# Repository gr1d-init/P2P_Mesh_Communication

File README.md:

# P2P_Mesh_Communication_Learning_Kit_SKEE1103_C_Programming_for_Engineers

For this project, our main targeted users were particularly the high school students who are able to comprehend most basic peer-to-peer mesh communication knowledge which often included in STEM subject syllabus such as Computer Science and Physics subject. 

Other than that, students are also exposed to an exciting involvement in Arduino kit development, lies under the usage of microcontrollers, which is a foundational skillset for their Reka Bentuk Teknologi subject that includes hardware and software implementations.

In short, we want student to head the ground up, build up a Peer-to-Peer Mesh Communication Device on their own with given instructions manual, enhance their practical skills on utilise a microcontroller and strengthen their understanding towards wireless communication protocols.

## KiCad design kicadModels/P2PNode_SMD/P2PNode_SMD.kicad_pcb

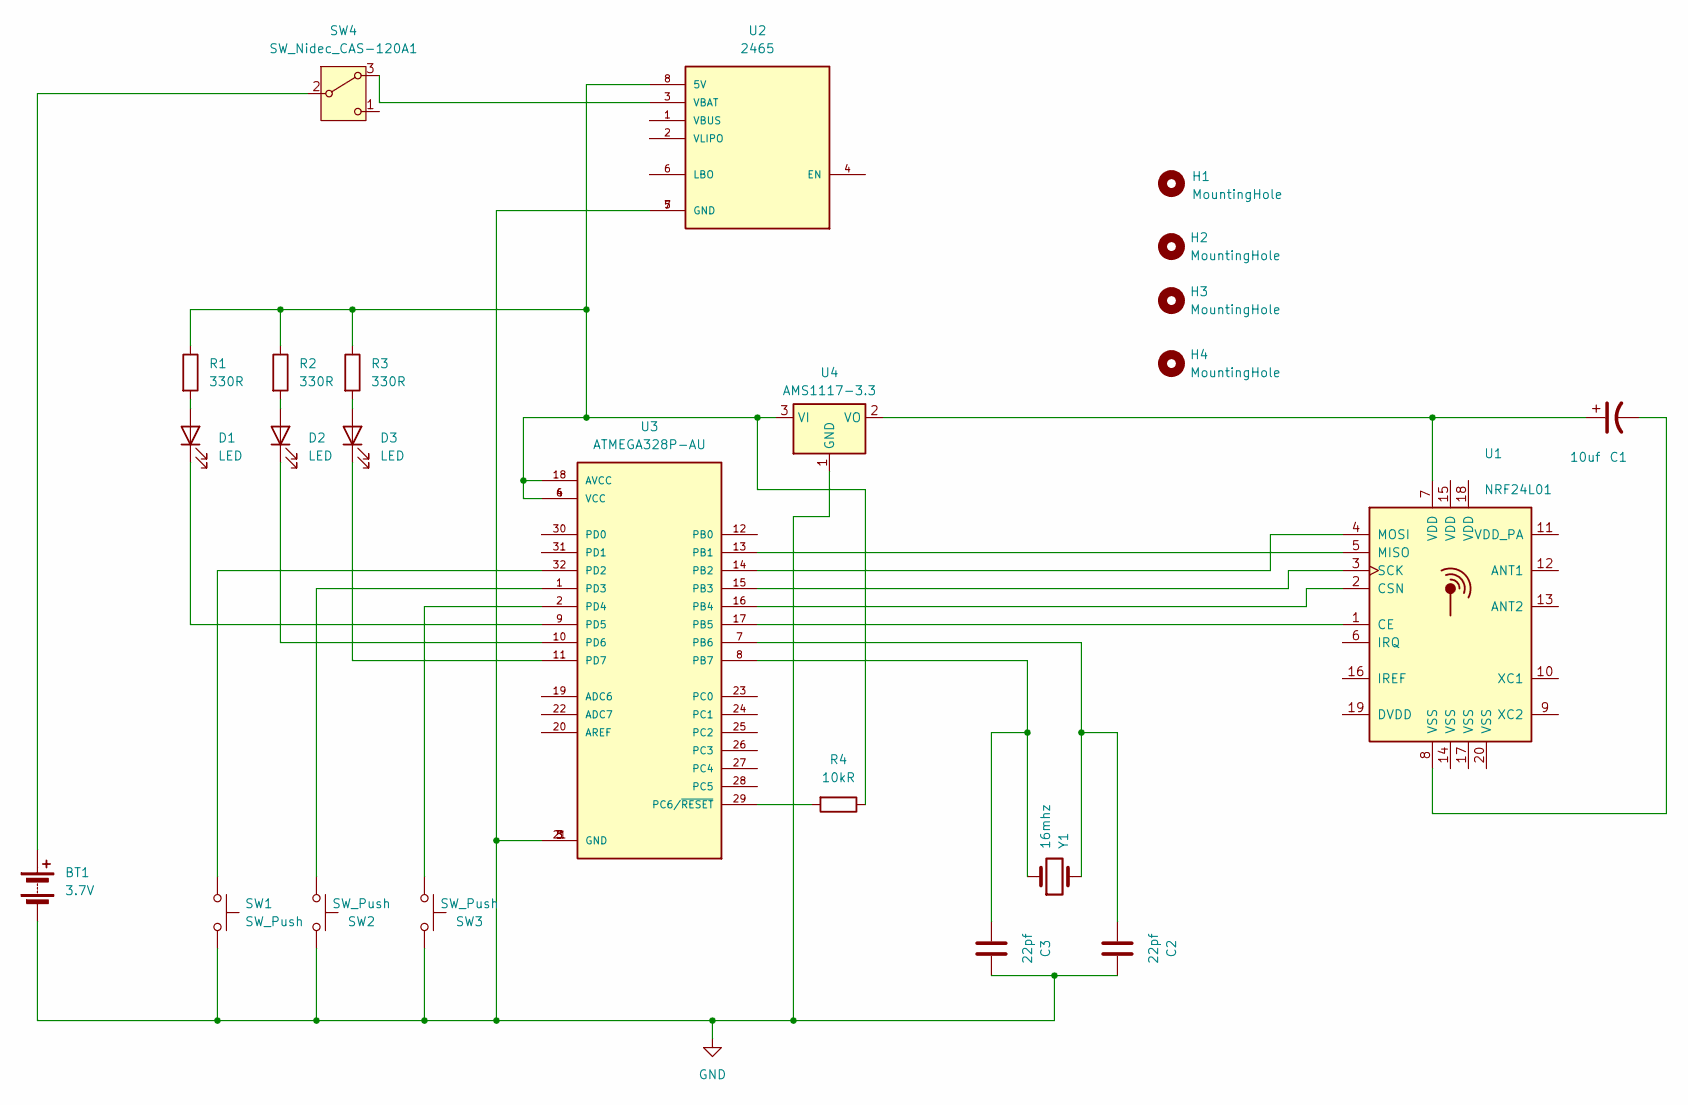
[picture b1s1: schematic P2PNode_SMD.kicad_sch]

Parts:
BT1: 3.7V; BatteryHolder_Keystone_1042_1x18650
C1: 10uf; C_0201_0603Metric
C2, C3: 22pf; C_0201_0603Metric
D1, D2, D3: LED; LED_1206_3216Metric
H1, H2, H3, H4: MountingHole; MountingHole_2.1mm
R1, R2, R3: 330R; R_0201_0603Metric
R4: 10kR; R_0201_0603Metric
SW1, SW2, SW3: SW_Push; SW_Push_1P1T_NO_CK_KMR2
SW4: SW_Nidec_CAS-120A1; Nidec_Copal_CAS-120A
U1: NRF24L01; QFN-20-1EP_4x4mm_P0.5mm_EP2.5x2.5mm
U2: 2465; MODULE_2465; PARTREV B
U3: ATMEGA328P-AU; QFP80P900X900X120-32N; PARTREV 8271A
U4: AMS1117-3.3; SOT-223-3_TabPin2
Y1: 16mhz; Crystal_SMD_Abracon_ABM7-2Pin_6.0x3.5mm

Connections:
GND: BT1.2 (-), C2.2, C3.2, SW1.2, SW2.2, SW3.2, U2.5 (GND), U2.7 (GND), U3.3 (GND), U3.5 (GND), U3.21 (GND), U4.1 (GND)
unnamed: BT1.1 (+), SW4.2 (B)
unnamed: C1.2, U1.8 (VSS)
unnamed: D1.2 (A), R1.2
unnamed: D1.1 (K), U3.9 (PD5)
unnamed: D2.2 (A), R2.2
unnamed: D2.1 (K), U3.10 (PD6)
unnamed: D3.2 (A), R3.2
unnamed: D3.1 (K), U3.11 (PD7)
unnamed: SW4.3 (A), U2.3 (VBAT)
unnamed: U1.1 (CE), U3.17 (PB5)
unnamed: U1.2 (CSN), U3.16 (PB4)
unnamed: U1.5 (MISO), U3.13 (PB1)
unnamed: U1.4 (MOSI), U3.14 (PB2)
unnamed: U1.3 (SCK), U3.15 (PB3)
unnamed: R1.1, R2.1, R3.1, R4.1, U2.8 (5V), U3.4 (VCC), U3.6 (VCC), U3.18 (AVCC), U4.3 (VI)
unnamed: C2.1, U3.7 (PB6), Y1.2
unnamed: C3.1, U3.8 (PB7), Y1.1
unnamed: R4.2, U3.29 (PC6/~RESET)
unnamed: SW1.1, U3.32 (PD2)
unnamed: SW2.1, U3.1 (PD3)
unnamed: SW3.1, U3.2 (PD4)
unnamed: C1.1, U1.7 (VDD), U4.2 (VO)

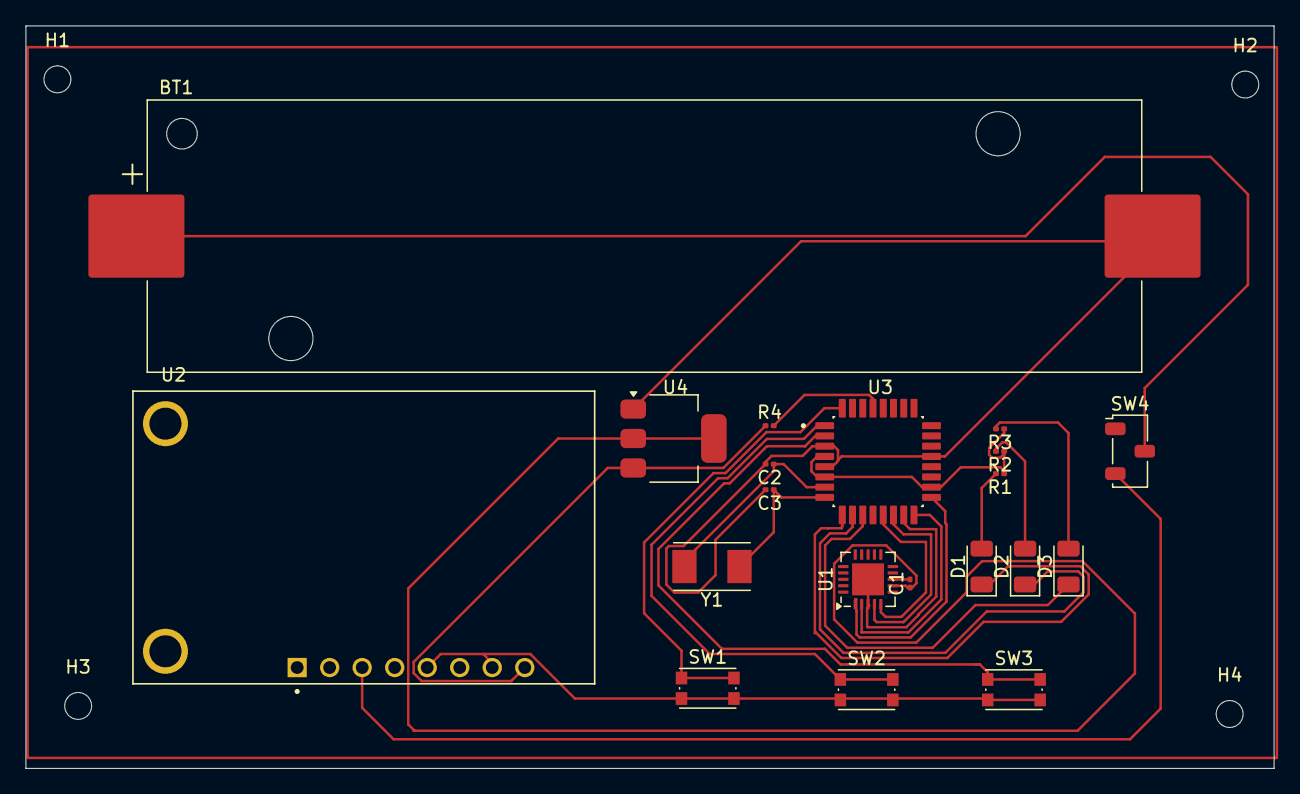
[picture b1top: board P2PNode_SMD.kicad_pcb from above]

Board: 2 copper layers, 97.5 x 58.0 mm, 24 parts (0 on the bottom side), 23 nets.

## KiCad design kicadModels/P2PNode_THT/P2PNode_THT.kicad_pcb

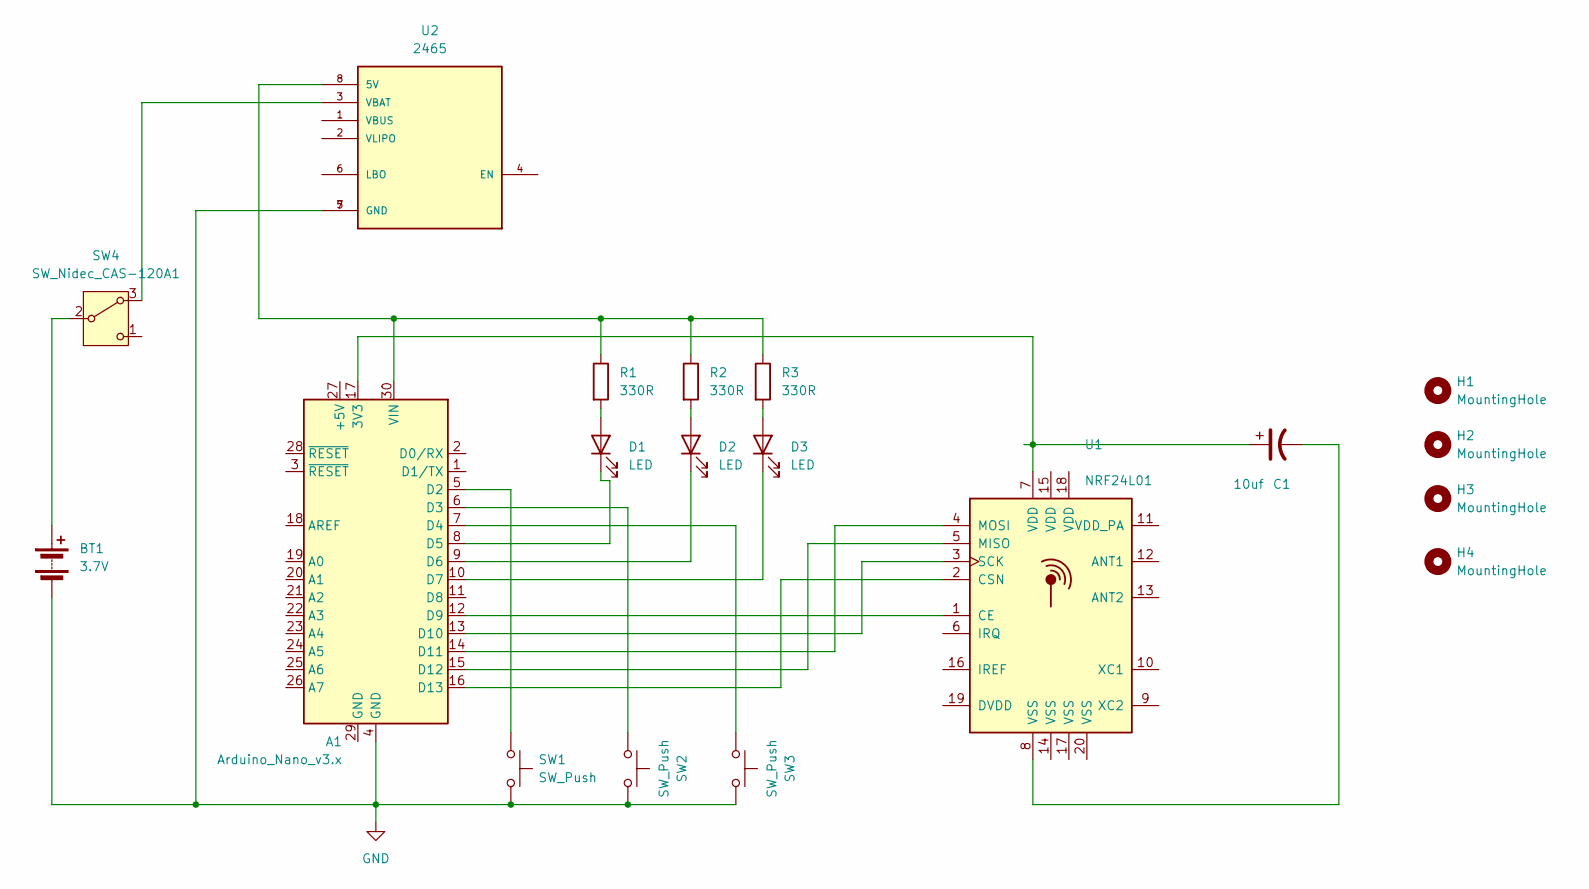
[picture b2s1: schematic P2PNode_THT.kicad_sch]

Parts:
A1: Arduino_Nano_v3.x; Arduino_Nano
BT1: 3.7V; BatteryHolder_Keystone_1042_1x18650
C1: 10uf; CP_Axial_L10.0mm_D4.5mm_P15.00mm_Horizontal
D1, D2, D3: LED; LED_D3.0mm
H1, H2, H3, H4: MountingHole; MountingHole_2.1mm
R1, R2, R3: 330R; R_Axial_DIN0204_L3.6mm_D1.6mm_P5.08mm_Horizontal
SW1, SW2, SW3: SW_Push; SW_PUSH_6mm_H5mm
SW4: SW_Nidec_CAS-120A1; Nidec_Copal_CAS-120A
U1: NRF24L01; QFN-20-1EP_4x4mm_P0.5mm_EP2.5x2.5mm
U2: 2465; MODULE_2465; PARTREV B

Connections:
GND: A1.4 (GND), BT1.2 (-), SW1.2, SW2.2, SW3.2, U2.5 (GND), U2.7 (GND)
unnamed: A1.17 (3V3), C1.1, U1.7 (VDD)
unnamed: A1.5 (D2), SW1.1
unnamed: A1.6 (D3), SW2.1
unnamed: A1.7 (D4), SW3.1
unnamed: A1.8 (D5), D1.1 (K)
unnamed: A1.9 (D6), D2.1 (K)
unnamed: A1.10 (D7), D3.1 (K)
unnamed: A1.12 (D9), U1.1 (CE)
unnamed: A1.13 (D10), U1.3 (SCK)
unnamed: A1.14 (D11), U1.4 (MOSI)
unnamed: A1.15 (D12), U1.5 (MISO)
unnamed: A1.16 (D13), U1.2 (CSN)
unnamed: A1.30 (VIN), R1.1, R2.1, R3.1, U2.8 (5V)
unnamed: BT1.1 (+), SW4.2 (B)
unnamed: C1.2, U1.8 (VSS)
unnamed: D1.2 (A), R1.2
unnamed: D2.2 (A), R2.2
unnamed: D3.2 (A), R3.2
unnamed: SW4.3 (A), U2.3 (VBAT)

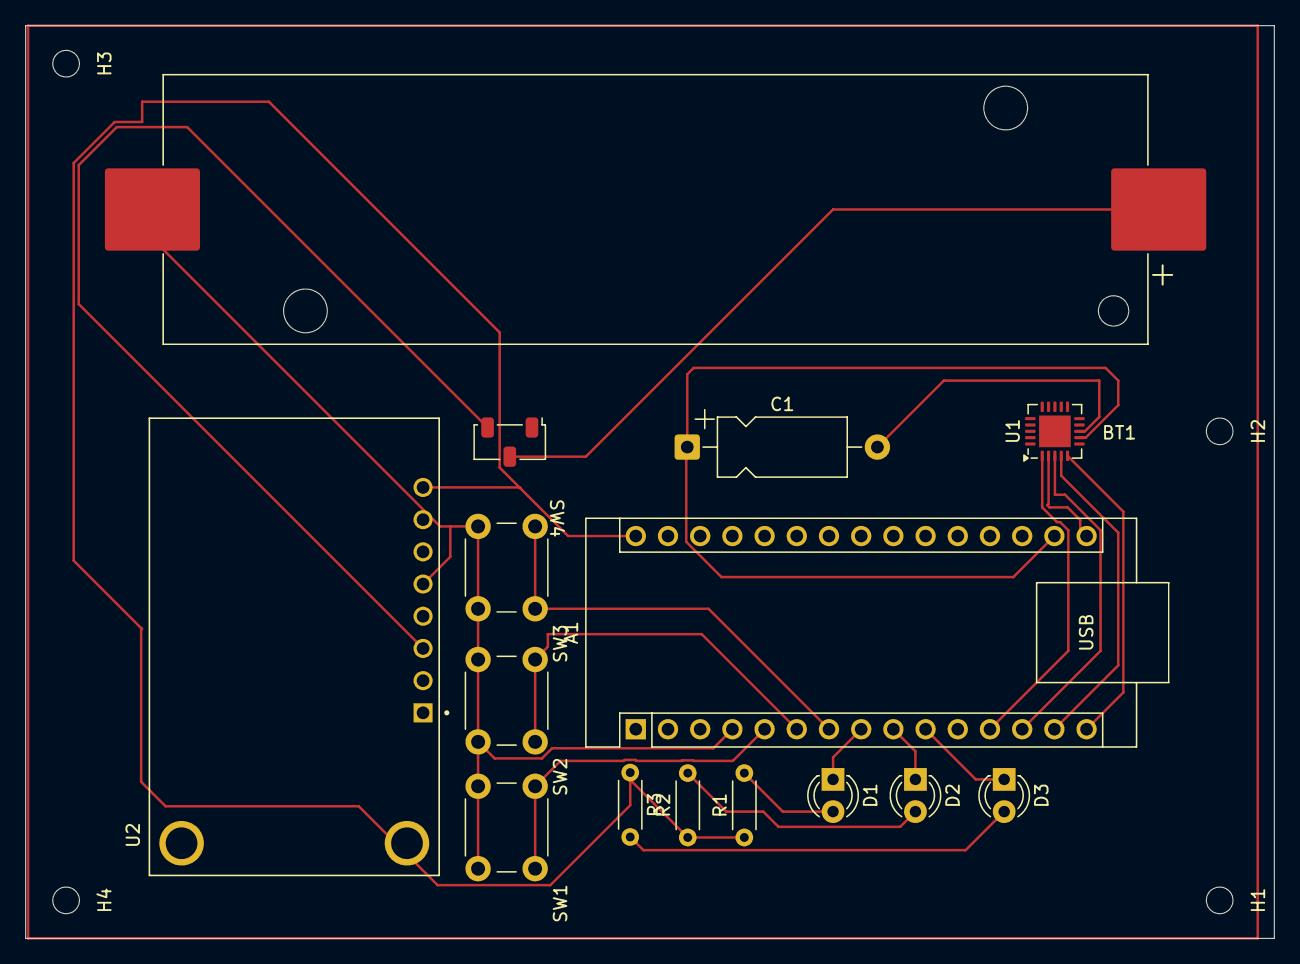
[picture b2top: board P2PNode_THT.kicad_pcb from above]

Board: 2 copper layers, 98.5 x 72.0 mm, 19 parts (0 on the bottom side), 20 nets.

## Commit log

2025-06-24 Create arduinoSketches
2025-06-24 Create test
